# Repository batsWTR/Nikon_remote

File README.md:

# Nikon_remote
An infra red remote for Nikon D50 type ML-L3

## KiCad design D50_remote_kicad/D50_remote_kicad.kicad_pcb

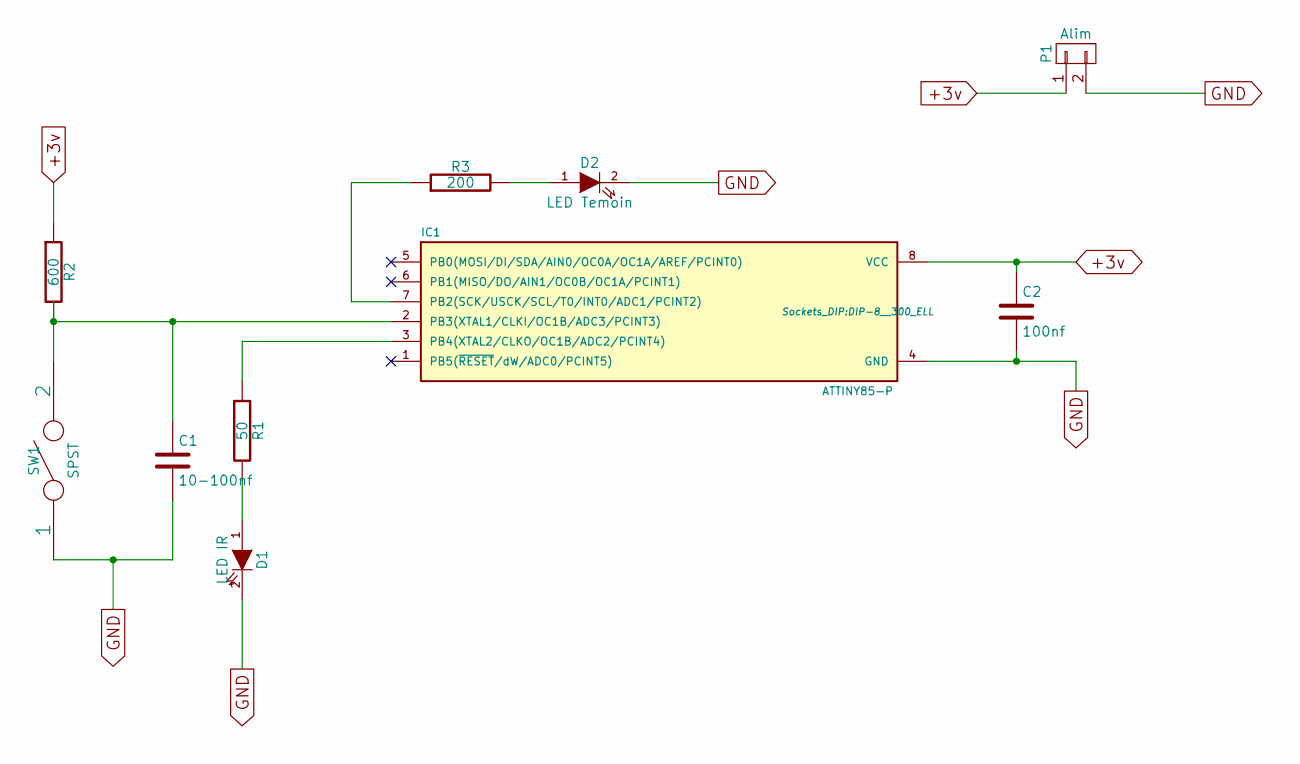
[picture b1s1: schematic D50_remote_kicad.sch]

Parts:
C1: 10-100nf; C1
C2: 100nf; C1
D1: LED IR; LED-3MM
D2: LED Temoin; LED-3MM
IC1: ATTINY85-P; DIP-8__300_ELL
P1: Alim; CR2032H
R1: 50; R3
R2: 600; R3
R3: 200; R3
SW1: SPST; push_mini

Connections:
+3v: C2.1, IC1.8 (VCC), P1.1, R2.1
GND: C1.2, C2.2, D1.2 (K), D2.2 (K), IC1.4 (GND), P1.2, SW1.1
unnamed: C1.1, IC1.2 (PB3(XTAL1/CLKI/OC1B/ADC3/PCINT3)), R2.2, SW1.2
unnamed: D1.1 (A), R1.2
unnamed: D2.1 (A), R3.2
unnamed: IC1.3 (PB4(XTAL2/CLKO/OC1B/ADC2/PCINT4)), R1.1
unnamed: IC1.7 (PB2(SCK/USCK/SCL/T0/INT0/ADC1/PCINT2)), R3.1

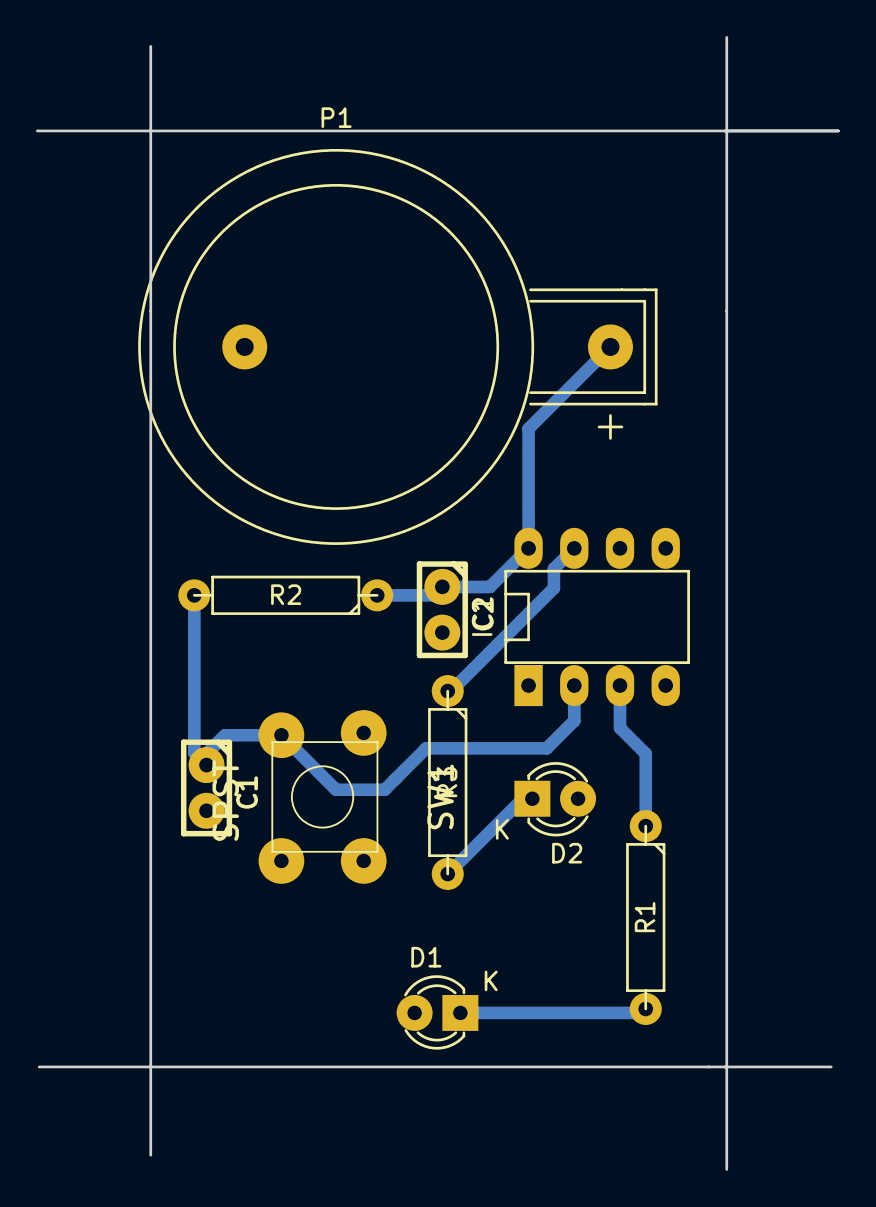
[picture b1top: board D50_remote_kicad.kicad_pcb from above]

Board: 2 copper layers, 44.5 x 62.9 mm, 10 parts (0 on the bottom side), 7 nets.
